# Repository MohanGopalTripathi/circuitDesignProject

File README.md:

# circuitDesignProject
Some projects developed on Eagle

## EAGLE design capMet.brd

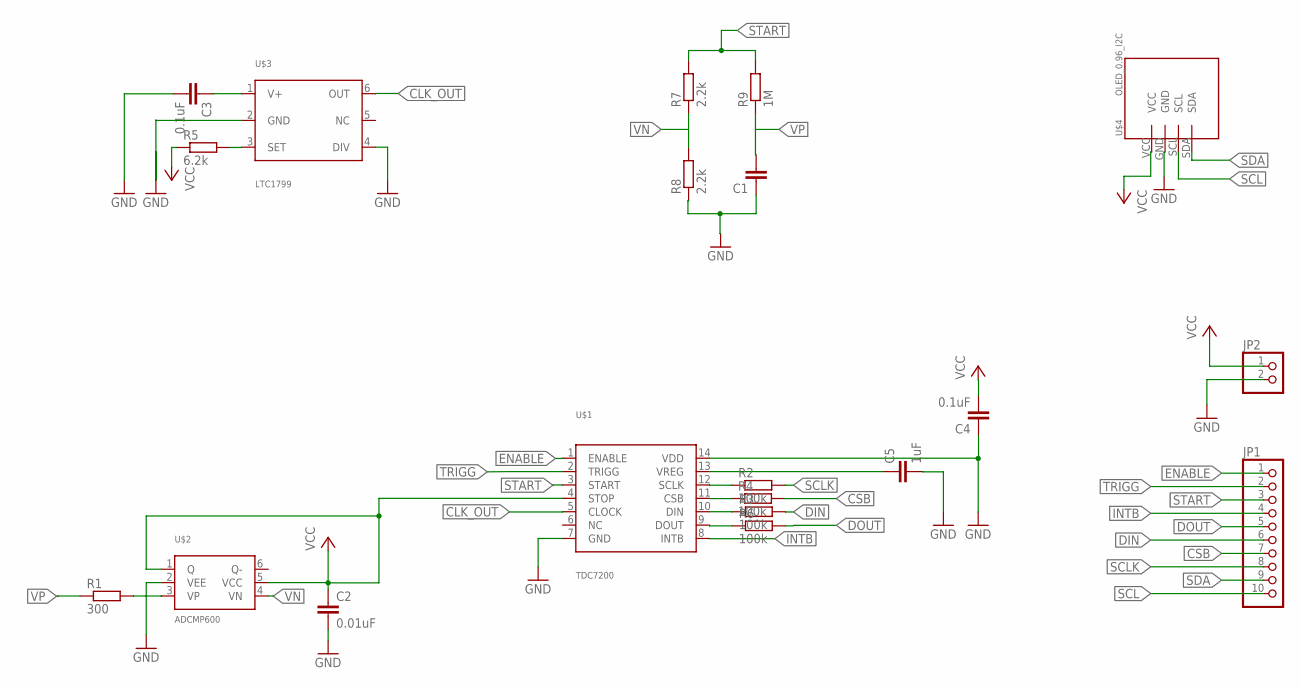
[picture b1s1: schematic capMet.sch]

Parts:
C1: C-EUC0805; C0805
C2: 0.01uF; C0805
C3, C4: 0.1uF; C0805
C5: 1uF; C0805
JP1: PINHD-1X10; 1X10
JP2: PINHD-1X2; 1X02
R1: 300; R0805
R2, R3, R4, R6: 100k; R0805
R5: 6.2k; R0805
R7, R8: 2.2k; R0805
R9: 1M; R0805
U$1: TDC7200; TSSOP14
U$2: ADCMP600; SC70-6
U$3: LTC1799; TSOT23-6
U$4: OLED_0.96_I2C

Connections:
CLK_OUT: U$3.6 (OUT)
CSB: JP1.7, R4.2
DIN: JP1.6, R3.2
DOUT: JP1.5, R6.2
ENABLE: JP1.1, U$1.1 (ENABLE)
GND: C1.1, C2.2, C3.2, C5.2, JP2.2, R8.1, U$1.7 (GND), U$2.2 (VEE), U$3.2 (GND), U$3.4 (DIV), U$4.GND
INTB: JP1.4, U$1.8 (INTB)
unnamed: C3.1, U$3.1 (V+)
unnamed: R5.2, U$3.3 (SET)
unnamed: R1.2, U$2.3 (VP)
unnamed: U$1.4 (STOP), U$2.1 (Q)
unnamed: R6.1, U$1.9 (DOUT)
unnamed: C5.1, U$1.13 (VREG)
unnamed: C4.1, U$1.14 (VDD)
unnamed: R7.1, R8.2
unnamed: C1.2, R9.1
SCL: JP1.10, U$4.SCL
SCLK: JP1.8, R2.2
SDA: JP1.9, U$4.SDA
START: JP1.3, R7.2, R9.2, U$1.3 (START)
TRIGG: JP1.2, U$1.2 (TRIGG)
VCC: C2.1, C4.2, JP2.1, R5.1, U$2.5 (VCC), U$4.VCC
VN: U$2.4 (VN)
VP: R1.1

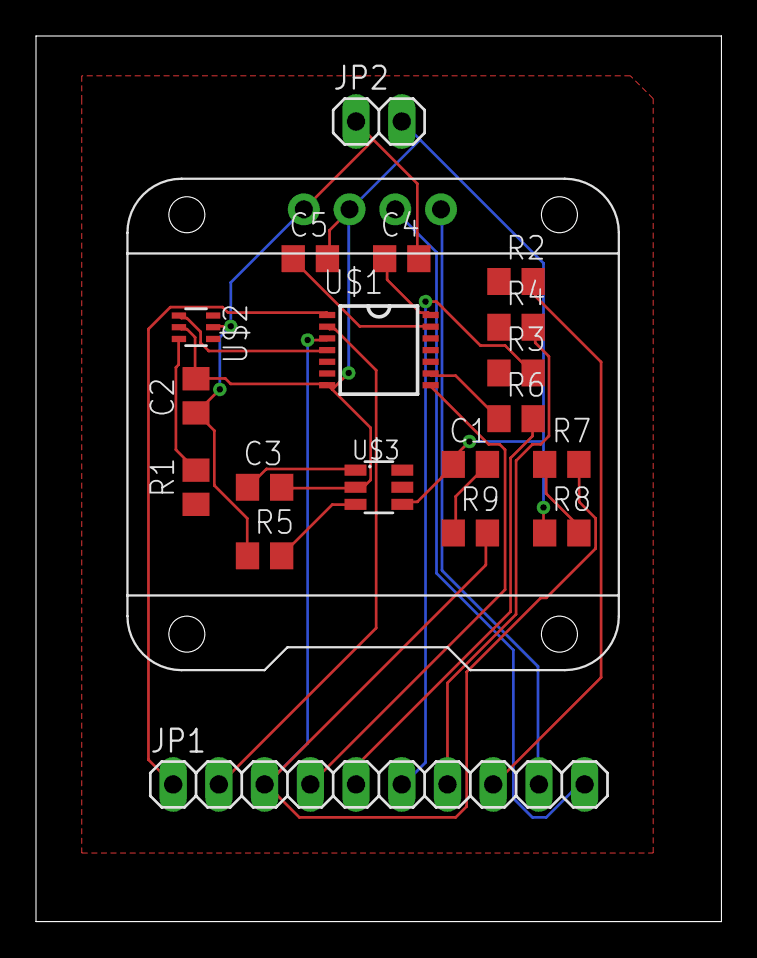
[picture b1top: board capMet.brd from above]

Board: 2 copper layers, 38.1 x 49.2 mm, 20 parts (0 on the bottom side), 21 nets.

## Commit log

2020-05-22 Schematic of the project
2020-05-22 PCB board file of the project
2020-05-22 png files
2020-05-22 png files for pcb board
